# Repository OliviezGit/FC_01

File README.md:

# FC_01

Projet KiCad H743_Ardupilot.

Le [dossier composants](composants/README.md) contient les fiches techniques PDF, bibliothèques locales, STEP, vues de contrôle et la nomenclature France du 27/09/2026.

- [Contrôle PDF complet](composants/controle/CONTROLE_COMPLET.pdf)
- [BOM France et références à commander](composants/BOM_FR.csv)
- [Rapport de vérification et réserves](verification/REPORT.md)

La présence des fichiers est vérifiée. La fabrication reste non libérée et quatre références fabricant restent sans offre France confirmée.

## État PCB

- PCB : **6 couches cuivre** configurées.
- Huaqiu 90 Ω : **0,2037 mm / 0,2451 mm** enregistré dans le projet.
- Routage : **0 piste, 0 via, 0 zone**.
- Revue CEM/implantation : voir [verification/REPORT.md](verification/REPORT.md).

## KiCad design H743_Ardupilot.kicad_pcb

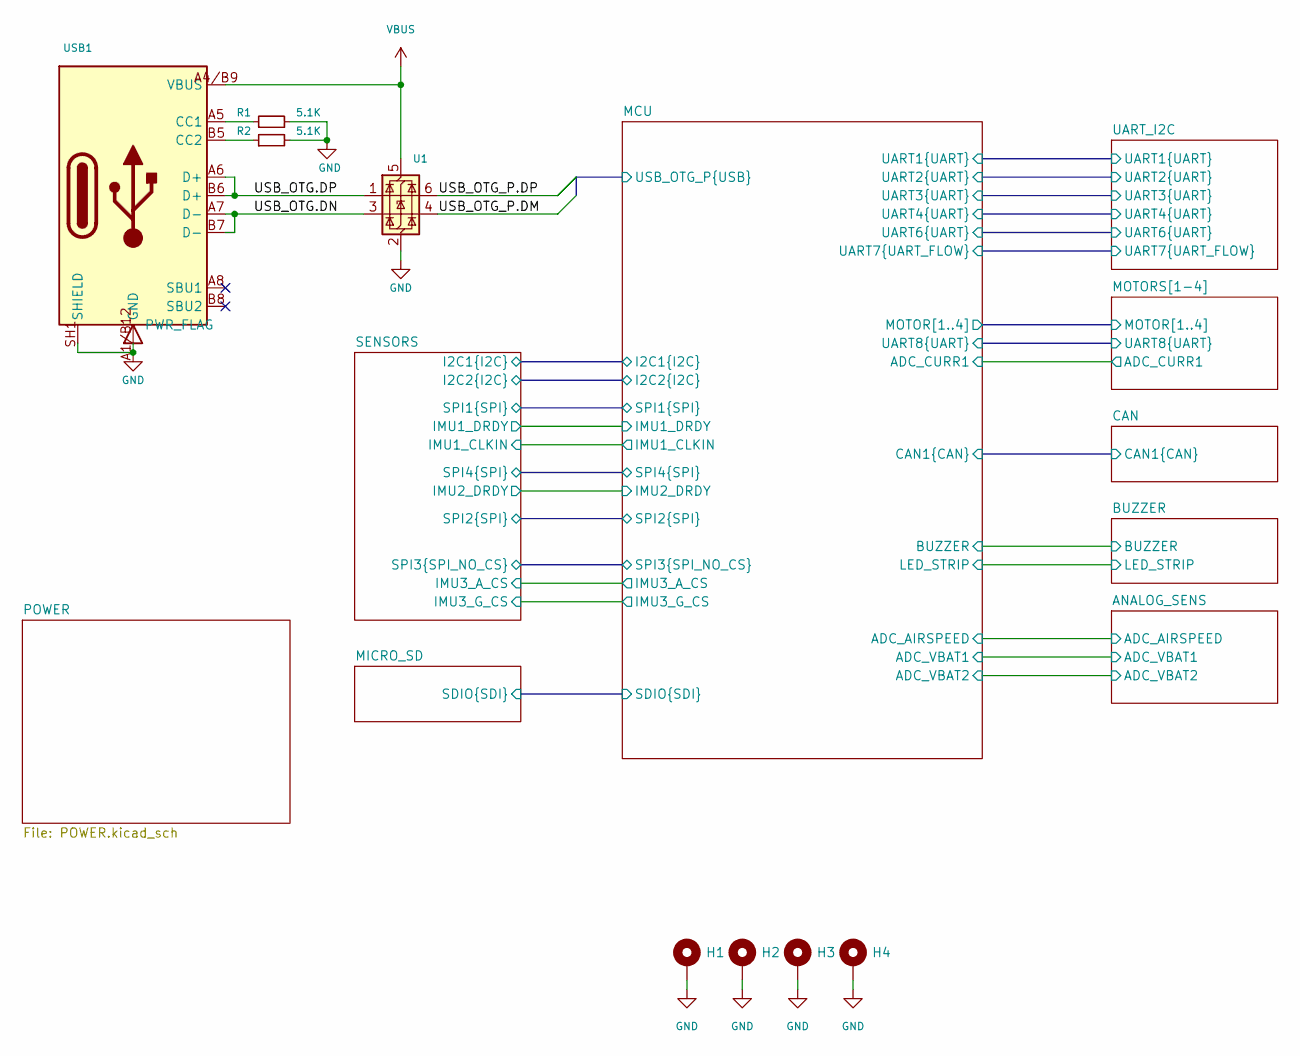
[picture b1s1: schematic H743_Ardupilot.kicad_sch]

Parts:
H1, H2, H3, H4: MountingHole_Pad; MountingHole_3.2mm_M3_ISO7380_Pad; DigiKey Status Element PCB; aucun composant achete
R1, R2: 5.1K; R_0402_1005Metric; MPN 0402WGF5101TCE; LCSC Part C25905
U1: USBLC6-2P6; SOT50P160X60-6N; MPN USBLC6-2P6; mouser 511-USBLC6-2P6
USB1: DX07S016JA1R1500; JAE_DX07S016JA1R1500_16P; MPN DX07S016JA1R1500; DigiKey Part Number 670-DX07S016JA1R1500CT-ND

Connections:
/MCU/USB_OTG_P.DM: U1.4 (I/O2); also elsewhere on the board
/MCU/USB_OTG_P.DP: U1.6 (I/O1); also elsewhere on the board
/USB_OTG.DN: U1.3 (I/O2), USB1.A7 (D-), USB1.B7 (D-)
/USB_OTG.DP: U1.1 (I/O1), USB1.A6 (D+), USB1.B6 (D+)
GND: H1.1 (1_1), H2.1 (1_1), H3.1 (1_1), H4.1 (1_1), R1.2, R2.2, U1.2 (GND), USB1.A1/B12 (GND), USB1.A12/B1 (GND), USB1.SH1 (SHIELD), USB1.SH2 (SHIELD), USB1.SH3 (SHIELD), USB1.SH4 (SHIELD), USB1.SH5 (SHIELD), USB1.SH6 (SHIELD); also elsewhere on the board
unnamed: R1.1, USB1.A5 (CC1)
unnamed: R2.1, USB1.B5 (CC2)
VBUS: U1.5 (VBUS), USB1.A4/B9 (VBUS), USB1.B4/A9 (VBUS); also elsewhere on the board

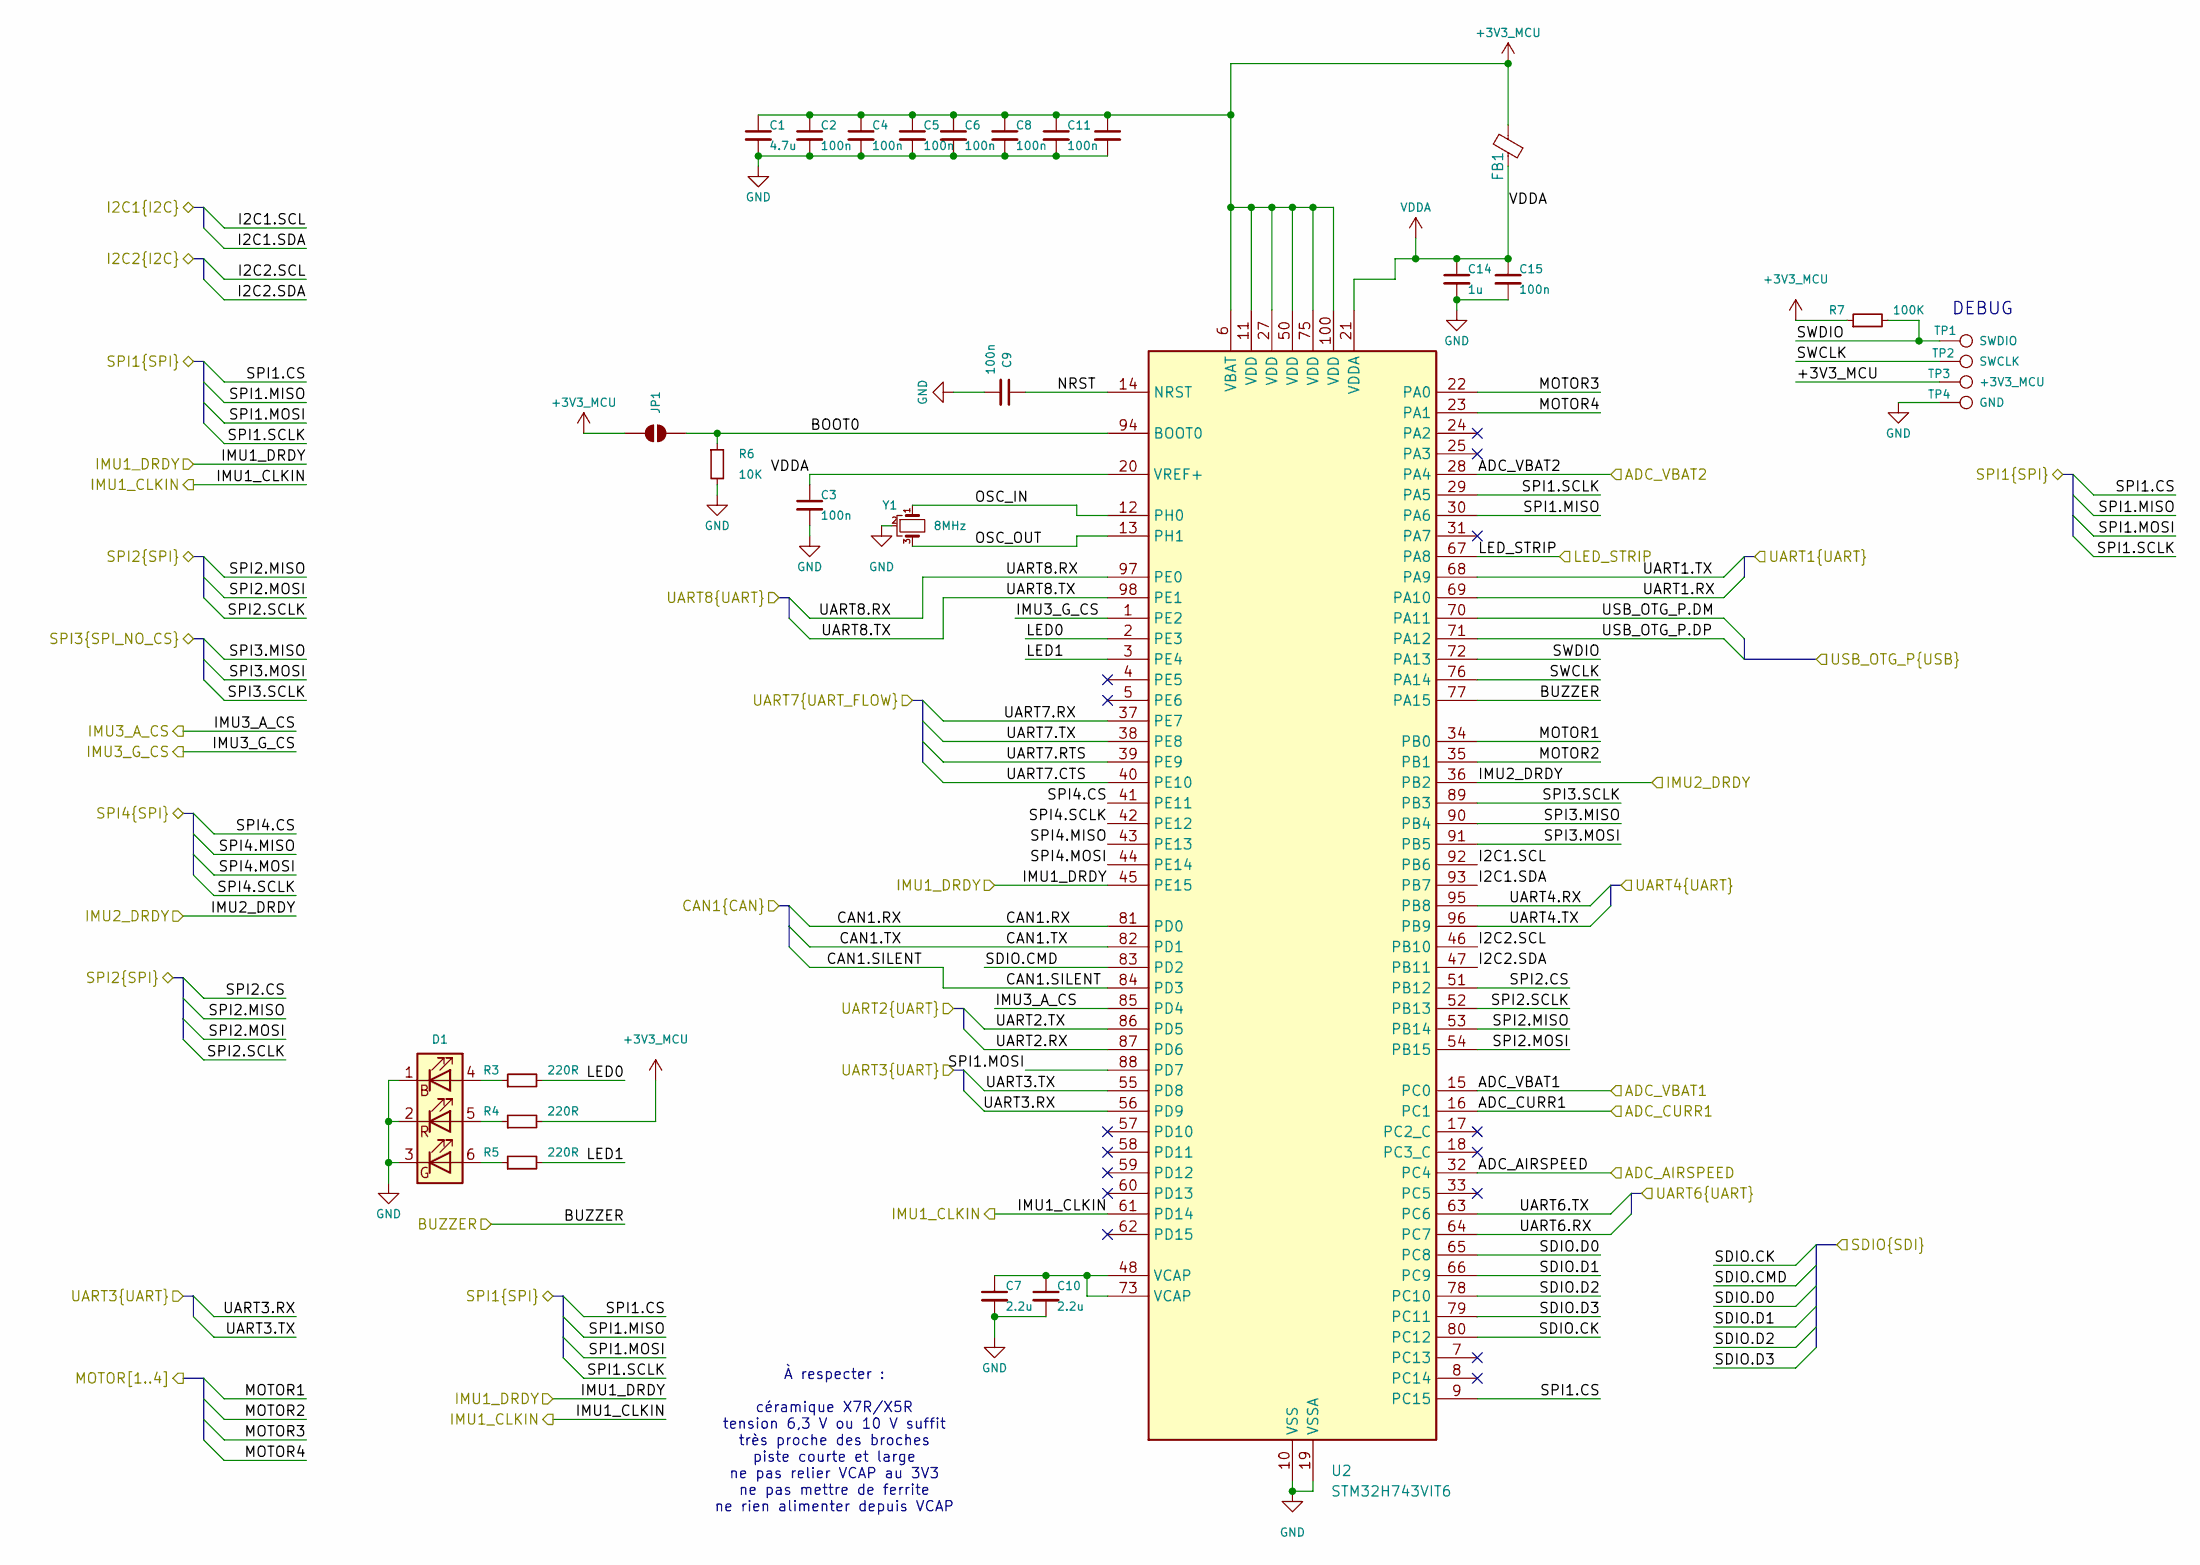
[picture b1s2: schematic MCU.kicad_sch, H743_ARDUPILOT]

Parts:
C1: 4.7u; C_0402_1005Metric; MPN CL05A475MP5NRNC; DigiKey Part Number 1276-1482-1-ND
C2, C3, C4, C5, C6, C8, C9, C11, C12, C15: 100n; C_0402_1005Metric; MPN CL05B104KO5NNNC; DigiKey Part Number 1276-1001-1-ND
C7, C10: 2.2u; C_0402_1005Metric; MPN C1005X5R1C225M050BC; DigiKey Specs 2.2 µF ±20%, 16 V, X5R, 0402
C14: 1u; C_0402_1005Metric; MPN CL05A105KA5NQNC; DigiKey Part Number 1276-1445-1-ND
D1: 19-337/R6GHBHC-M01/2T; Everlight_19-337_1.6x1.6mm; MPN 19-337/R6GHBHC-M01/2T; LCSC Part C131204
FB1: 600Ω@100MHz; L_0402_1005Metric; MPN BLM15AG601SN1D; DigiKey Part Number 490-1006-1-ND
JP1: SolderJumper_2_Open; SolderJumper-2_P1.3mm_Open_RoundedPad1.0x1.5mm; DigiKey Status Element PCB; aucun composant achete
R3, R4, R5: 220R; R_0402_1005Metric; MPN RC0402FR-07220RL; DigiKey Specs 220 Ω ±1%, 0402
R6: 10K; R_0402_1005Metric; MPN RC0402FR-0710KL; DigiKey Specs 10 kΩ ±1%, 0402
R7: 100K; R_0402_1005Metric; MPN RC0402FR-07100KL; DigiKey Specs 100 kΩ ±1%, 0402
TP1: SWDIO; TestPoint_Pad_1.0x1.0mm; DigiKey Status Element PCB; aucun composant achete
TP2: SWCLK; TestPoint_Pad_1.0x1.0mm; DigiKey Status Element PCB; aucun composant achete
TP3: +3V3_MCU; TestPoint_Pad_1.0x1.0mm; DigiKey Status Element PCB; aucun composant achete
TP4: GND; TestPoint_Pad_1.0x1.0mm; DigiKey Status Element PCB; aucun composant achete
U2: STM32H743VIT6; LQFP-100_14x14mm_P0.5mm; MPN STM32H743VIT6; DigiKey Part Number 497-17720-ND
Y1: 8MHz; Murata_CSTNE_3.2x1.3_P1.2mm; MPN CSTNE8M00GH5C000R0; LCSC Part C341525

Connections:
+3V3_MCU: C1.1, C2.1, C4.1, C5.1, C6.1, C8.1, C11.1, C12.1, FB1.2, JP1.2 (B), R4.2, R7.1, TP3.1 (1_1), U2.6 (VBAT), U2.11 (VDD), U2.27 (VDD), U2.50 (VDD), U2.75 (VDD), U2.100 (VDD); also elsewhere on the board
/ANALOG_SENS/ADC_AIRSPEED: U2.32 (PC4); also elsewhere on the board
/ANALOG_SENS/ADC_VBAT1: U2.15 (PC0); also elsewhere on the board
/ANALOG_SENS/ADC_VBAT2: U2.28 (PA4); also elsewhere on the board
/BUZZER/BUZZER: U2.77 (PA15); also elsewhere on the board
/BUZZER/LED_STRIP: U2.67 (PA8); also elsewhere on the board
/CAN/CAN1.RX: U2.81 (PD0); also elsewhere on the board
/CAN/CAN1.SILENT: U2.84 (PD3); also elsewhere on the board
/CAN/CAN1.TX: U2.82 (PD1); also elsewhere on the board
/MCU/ADC_CURR1: U2.16 (PC1); also elsewhere on the board
/MCU/BOOT0: JP1.1 (A), R6.1, U2.94 (BOOT0)
/MCU/I2C1.SCL: U2.92 (PB6); also elsewhere on the board
/MCU/I2C1.SDA: U2.93 (PB7); also elsewhere on the board
/MCU/I2C2.SCL: U2.46 (PB10); also elsewhere on the board
/MCU/I2C2.SDA: U2.47 (PB11); also elsewhere on the board
/MCU/IMU1_CLKIN: U2.61 (PD14); also elsewhere on the board
/MCU/IMU1_DRDY: U2.45 (PE15); also elsewhere on the board
/MCU/IMU2_DRDY: U2.36 (PB2); also elsewhere on the board
/MCU/IMU3_A_CS: U2.85 (PD4); also elsewhere on the board
/MCU/IMU3_G_CS: U2.1 (PE2); also elsewhere on the board
/MCU/LED0: R3.2, U2.2 (PE3)
/MCU/LED1: R5.2, U2.3 (PE4)
/MCU/MOTOR1: U2.34 (PB0); also elsewhere on the board
/MCU/MOTOR2: U2.35 (PB1); also elsewhere on the board
/MCU/MOTOR3: U2.22 (PA0); also elsewhere on the board
/MCU/MOTOR4: U2.23 (PA1); also elsewhere on the board
/MCU/NRST: C9.1, U2.14 (NRST)
/MCU/OSC_IN: U2.12 (PH0), Y1.1
/MCU/OSC_OUT: U2.13 (PH1), Y1.3
/MCU/SDIO.CK: U2.80 (PC12); also elsewhere on the board
/MCU/SDIO.CMD: U2.83 (PD2); also elsewhere on the board
/MCU/SDIO.D0: U2.65 (PC8); also elsewhere on the board
/MCU/SDIO.D1: U2.66 (PC9); also elsewhere on the board
/MCU/SDIO.D2: U2.78 (PC10); also elsewhere on the board
/MCU/SDIO.D3: U2.79 (PC11); also elsewhere on the board
/MCU/SPI1.CS: U2.9 (PC15); also elsewhere on the board
/MCU/SPI1.MISO: U2.30 (PA6); also elsewhere on the board
/MCU/SPI1.MOSI: U2.88 (PD7); also elsewhere on the board
/MCU/SPI1.SCLK: U2.29 (PA5); also elsewhere on the board
/MCU/SPI2.CS: U2.51 (PB12); also elsewhere on the board
/MCU/SPI2.MISO: U2.53 (PB14); also elsewhere on the board
/MCU/SPI2.MOSI: U2.54 (PB15); also elsewhere on the board
/MCU/SPI2.SCLK: U2.52 (PB13); also elsewhere on the board
/MCU/SPI3.MISO: U2.90 (PB4); also elsewhere on the board
/MCU/SPI3.MOSI: U2.91 (PB5); also elsewhere on the board
/MCU/SPI3.SCLK: U2.89 (PB3); also elsewhere on the board
/MCU/SPI4.CS: U2.41 (PE11); also elsewhere on the board
/MCU/SPI4.MISO: U2.43 (PE13); also elsewhere on the board
/MCU/SPI4.MOSI: U2.44 (PE14); also elsewhere on the board
/MCU/SPI4.SCLK: U2.42 (PE12); also elsewhere on the board
/MCU/SWCLK: TP2.1 (1_1), U2.76 (PA14)
/MCU/SWDIO: R7.2, TP1.1 (1_1), U2.72 (PA13)
/MCU/UART1.RX: U2.69 (PA10); also elsewhere on the board
/MCU/UART1.TX: U2.68 (PA9); also elsewhere on the board
/MCU/UART2.RX: U2.87 (PD6); also elsewhere on the board
/MCU/UART2.TX: U2.86 (PD5); also elsewhere on the board
/MCU/UART3.RX: U2.56 (PD9); also elsewhere on the board
/MCU/UART3.TX: U2.55 (PD8); also elsewhere on the board
/MCU/UART4.RX: U2.95 (PB8); also elsewhere on the board
/MCU/UART4.TX: U2.96 (PB9); also elsewhere on the board
/MCU/UART6.RX: U2.64 (PC7); also elsewhere on the board
/MCU/UART6.TX: U2.63 (PC6); also elsewhere on the board
/MCU/UART7.CTS: U2.40 (PE10); also elsewhere on the board
/MCU/UART7.RTS: U2.39 (PE9); also elsewhere on the board
/MCU/UART7.RX: U2.37 (PE7); also elsewhere on the board
/MCU/UART7.TX: U2.38 (PE8); also elsewhere on the board
/MCU/UART8.RX: U2.97 (PE0); also elsewhere on the board
/MCU/UART8.TX: U2.98 (PE1)
/MCU/USB_OTG_P.DM: U2.70 (PA11); also elsewhere on the board
/MCU/USB_OTG_P.DP: U2.71 (PA12); also elsewhere on the board
GND: C1.2, C2.2, C3.2, C4.2, C5.2, C6.2, C7.2, C8.2, C9.2, C10.2, C11.2, C12.2, C14.2, C15.2, D1.1 (BK), D1.2 (RK), D1.3 (GK), R6.2, TP4.1 (1_1), U2.10 (VSS), U2.19 (VSSA), U2.26 (VSS), U2.49 (VSS), U2.74 (VSS), U2.99 (VSS), Y1.2; also elsewhere on the board
unnamed: C7.1, C10.1, U2.48 (VCAP), U2.73 (VCAP)
unnamed: D1.4 (BA), R3.1
unnamed: D1.6 (GA), R5.1
unnamed: D1.5 (RA), R4.1
VDDA: C3.1, C14.1, C15.1, FB1.1, U2.20 (VREF+), U2.21 (VDDA)

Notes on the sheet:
DEBUG
À respecter : céramique X7R/X5R tension 6,3 V ou 10 V suffit très proche des broches piste courte et large ne pas relier VCAP au 3V3 ne pas mettre de ferrite ne rien alimenter depuis VCAP

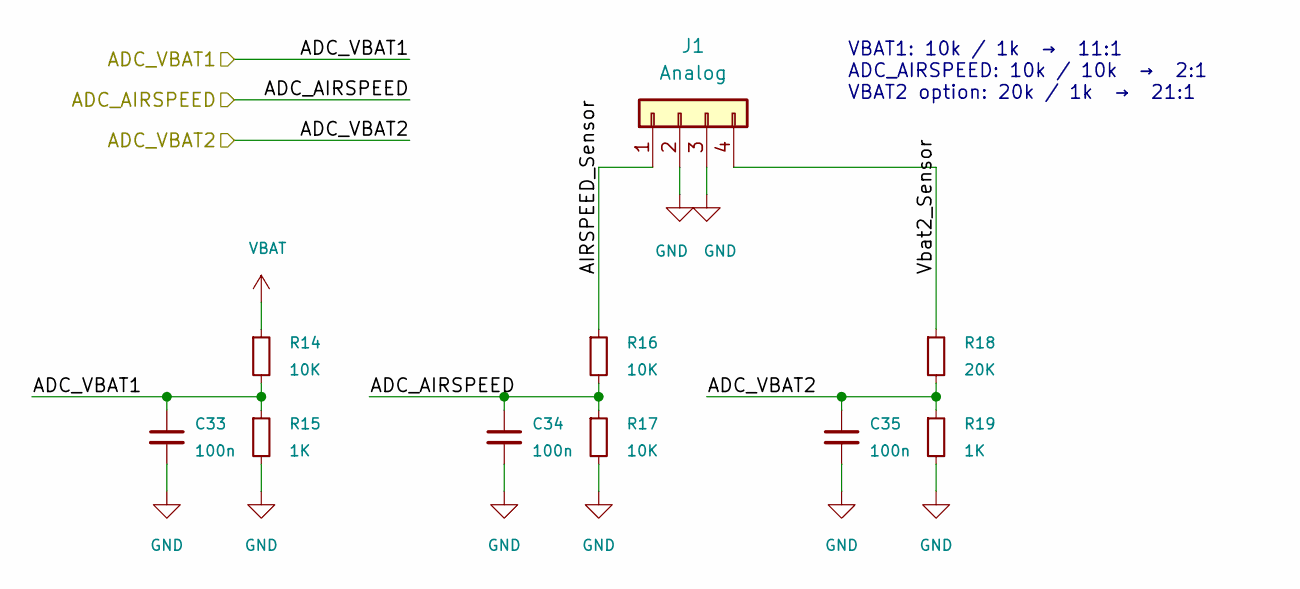
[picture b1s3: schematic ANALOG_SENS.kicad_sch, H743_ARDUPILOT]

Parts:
C33, C34, C35: 100n; C_0402_1005Metric; MPN CL05B104KO5NNNC; DigiKey Part Number 1276-1001-1-ND
J1: Analog; SolderPadArray_1x04_P2.54mm_1x1mm; DigiKey Status Element PCB; aucun composant achete
R14, R16, R17: 10K; R_0402_1005Metric; MPN RC0402FR-0710KL; DigiKey Specs 10 kΩ ±1%, 0402
R15, R19: 1K; R_0402_1005Metric; MPN RC0402FR-071KL; DigiKey Specs 1 kΩ ±1%, 0402
R18: 20K; R_0402_1005Metric; MPN RC0402FR-0720KL; DigiKey Specs 20 kΩ ±1%, 0402

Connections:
/ANALOG_SENS/ADC_AIRSPEED: C34.1, R16.2, R17.1; also elsewhere on the board
/ANALOG_SENS/ADC_VBAT1: C33.1, R14.2, R15.1; also elsewhere on the board
/ANALOG_SENS/ADC_VBAT2: C35.1, R18.2, R19.1; also elsewhere on the board
/ANALOG_SENS/AIRSPEED_Sensor: J1.1, R16.1
/ANALOG_SENS/Vbat2_Sensor: J1.4, R18.1
GND: C33.2, C34.2, C35.2, J1.2, J1.3, R15.2, R17.2, R19.2; also elsewhere on the board
VBAT: R14.1; also elsewhere on the board

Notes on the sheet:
VBAT1: 10k / 1k → 11:1 ADC_AIRSPEED: 10k / 10k → 2:1 VBAT2 option: 20k / 1k → 21:1

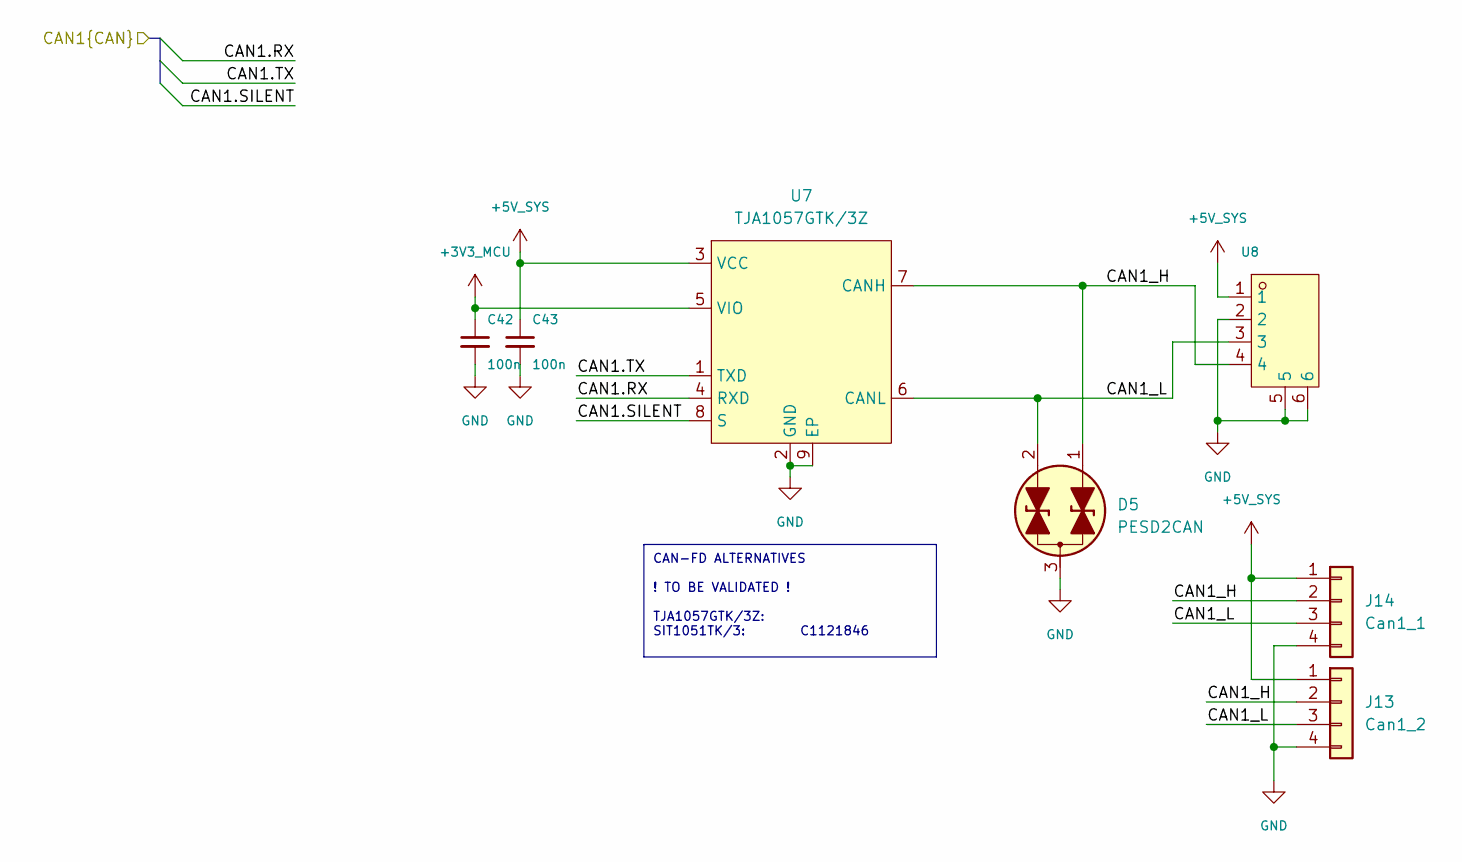
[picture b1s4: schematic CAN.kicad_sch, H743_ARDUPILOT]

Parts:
C42, C43: 100n; C_0402_1005Metric; MPN CL05B104KO5NNNC; DigiKey Part Number 1276-1001-1-ND
D5: PESD2CAN; SOT-23; MPN PESD2CANFD24V-TR; LCSC Part C552486
J13: Can1_2; SolderPadArray_1x04_P2.54mm_1x1mm; DigiKey Status Element PCB; aucun composant achete
J14: Can1_1; SolderPadArray_1x04_P2.54mm_1x1mm; DigiKey Status Element PCB; aucun composant achete
U7: TJA1057GTK/3Z; HVSON-8-1EP_3x3mm_P0.65mm_EP1.6x2.4mm; MPN TJA1057GTK/3Z; DigiKey Specs CAN 5 Mbps, 4.5–5.5 V, 8-HVSON 3x3
U8: SM04B-GHS-TB(LF)(SN); JST_GH_SM04B-GHS-TB_1x04_P1.25mm_Horizontal_GNDtabs; MPN SM04B-GHS-TB(LF)(SN); LCSC Part C7430446

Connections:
+3V3_MCU: C42.1, U7.5 (VIO); also elsewhere on the board
+5V_SYS: C43.1, J13.1, J14.1, U7.3 (VCC), U8.1; also elsewhere on the board
/CAN/CAN1.RX: U7.4 (RXD); also elsewhere on the board
/CAN/CAN1.SILENT: U7.8 (S); also elsewhere on the board
/CAN/CAN1.TX: U7.1 (TXD); also elsewhere on the board
/CAN/CAN1_H: D5.1 (K1), J13.2, J14.2, U7.7 (CANH), U8.4
/CAN/CAN1_L: D5.2 (K2), J13.3, J14.3, U7.6 (CANL), U8.3
GND: C42.2, C43.2, D5.3 (CC), J13.4, J14.4, U7.2 (GND), U7.9 (EP), U8.2, U8.5, U8.6; also elsewhere on the board

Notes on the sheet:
CAN-FD ALTERNATIVES ! TO BE VALIDATED ! TJA1057GTK/3Z: SIT1051TK/3: C1121846

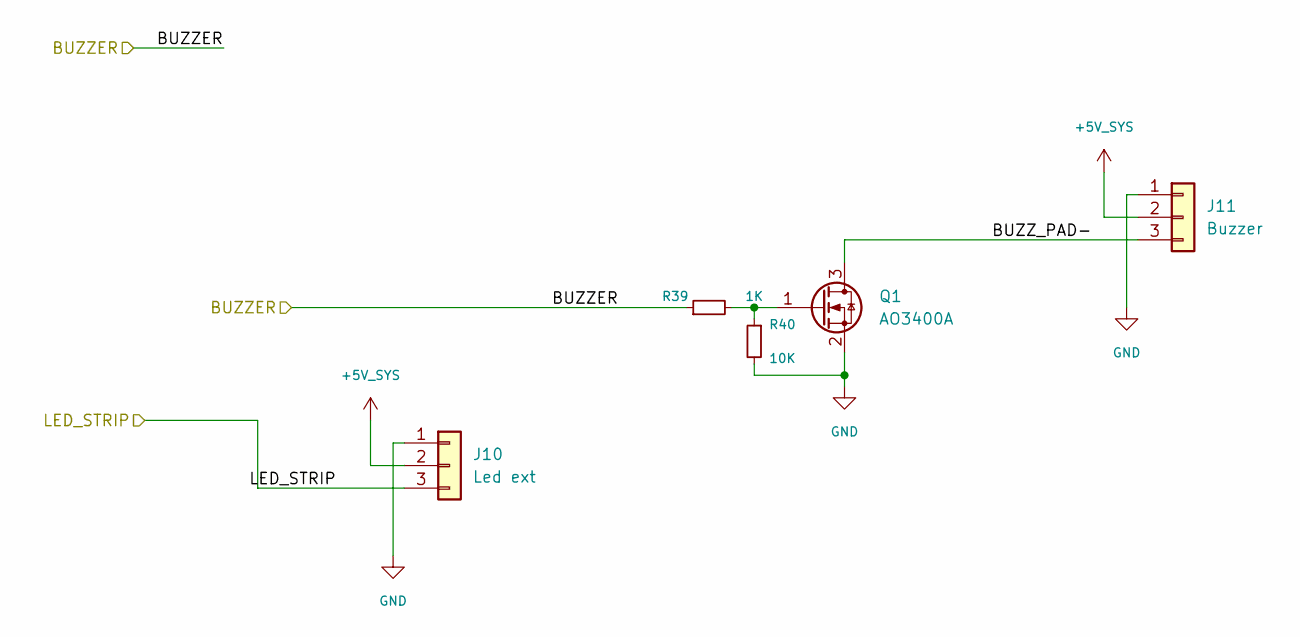
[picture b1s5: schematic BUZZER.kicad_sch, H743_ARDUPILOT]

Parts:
J10: Led ext; SolderPadArray_1x03_P2.54mm_1x1mm; DigiKey Status Element PCB; aucun composant achete
J11: Buzzer; SolderPadArray_1x03_P2.54mm_1x1mm; DigiKey Status Element PCB; aucun composant achete
Q1: AO3400A; SOT-23; MPN AO3400A; LCSC Part C20917
R39: 1K; R_0402_1005Metric; MPN RC0402FR-071KL; DigiKey Specs 1K ±1%, 0402 (1005), thick film
R40: 10K; R_0402_1005Metric; MPN RC0402FR-0710KL; DigiKey Specs 10K ±1%, 0402 (1005), thick film

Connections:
+5V_SYS: J10.2, J11.2; also elsewhere on the board
/BUZZER/BUZZER: R39.1; also elsewhere on the board
/BUZZER/BUZZ_PAD-: J11.3, Q1.3 (D)
/BUZZER/LED_STRIP: J10.3; also elsewhere on the board
GND: J10.1, J11.1, Q1.2 (S), R40.2; also elsewhere on the board
unnamed: Q1.1 (G), R39.2, R40.1

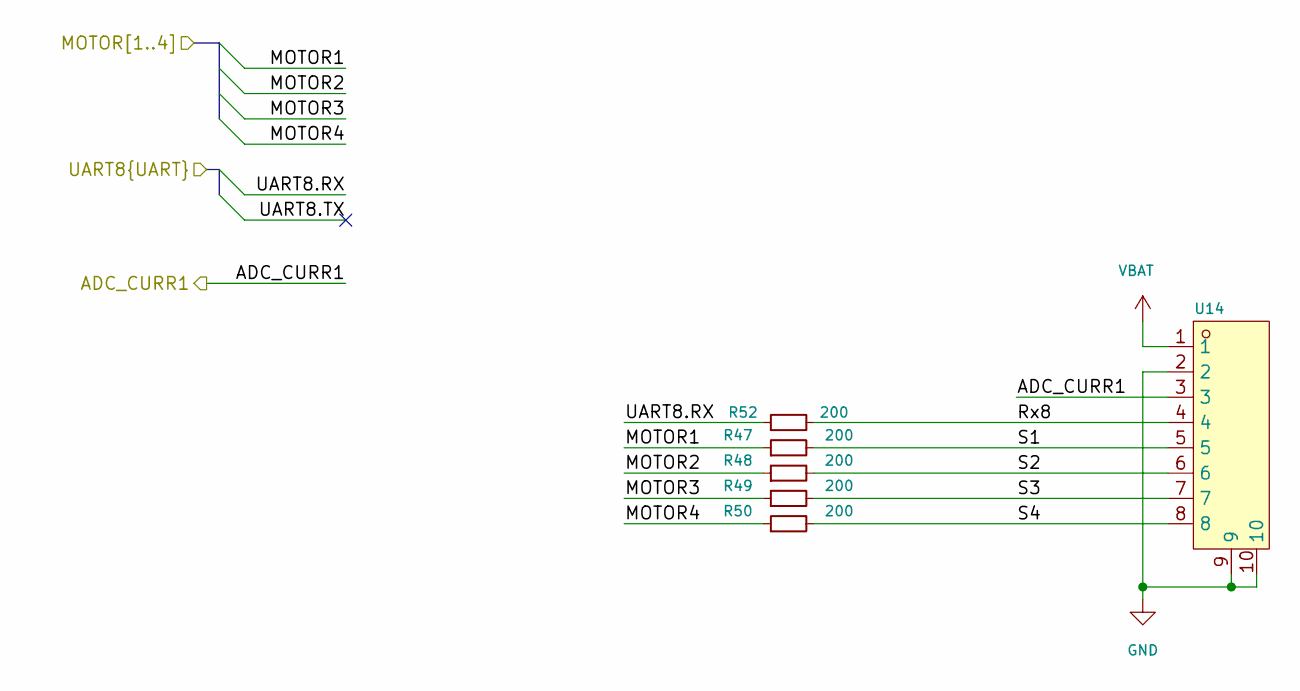
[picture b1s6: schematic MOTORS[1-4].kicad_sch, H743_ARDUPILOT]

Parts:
R47, R48, R49, R50, R52: 200; R_0402_1005Metric; MPN RC0402FR-07200RL; DigiKey Specs 200 ±1%, 0402 (1005), thick film
U14: SM08B-SRSS-TB(LF)(SN); JST_SH_SM08B-SRSS-TB_1x08_P1.00mm_Horizontal_GNDtabs; MPN SM08B-SRSS-TB(LF)(SN); LCSC Part C7430450

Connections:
/MCU/ADC_CURR1: U14.3; also elsewhere on the board
/MCU/MOTOR1: R47.1; also elsewhere on the board
/MCU/MOTOR2: R48.1; also elsewhere on the board
/MCU/MOTOR3: R49.1; also elsewhere on the board
/MCU/MOTOR4: R50.1; also elsewhere on the board
/MCU/UART8.RX: R52.1; also elsewhere on the board
/MOTORS[1-4]/Rx8: R52.2, U14.4
/MOTORS[1-4]/S1: R47.2, U14.5
/MOTORS[1-4]/S2: R48.2, U14.6
/MOTORS[1-4]/S3: R49.2, U14.7
/MOTORS[1-4]/S4: R50.2, U14.8
GND: U14.2, U14.9, U14.10; also elsewhere on the board
VBAT: U14.1; also elsewhere on the board

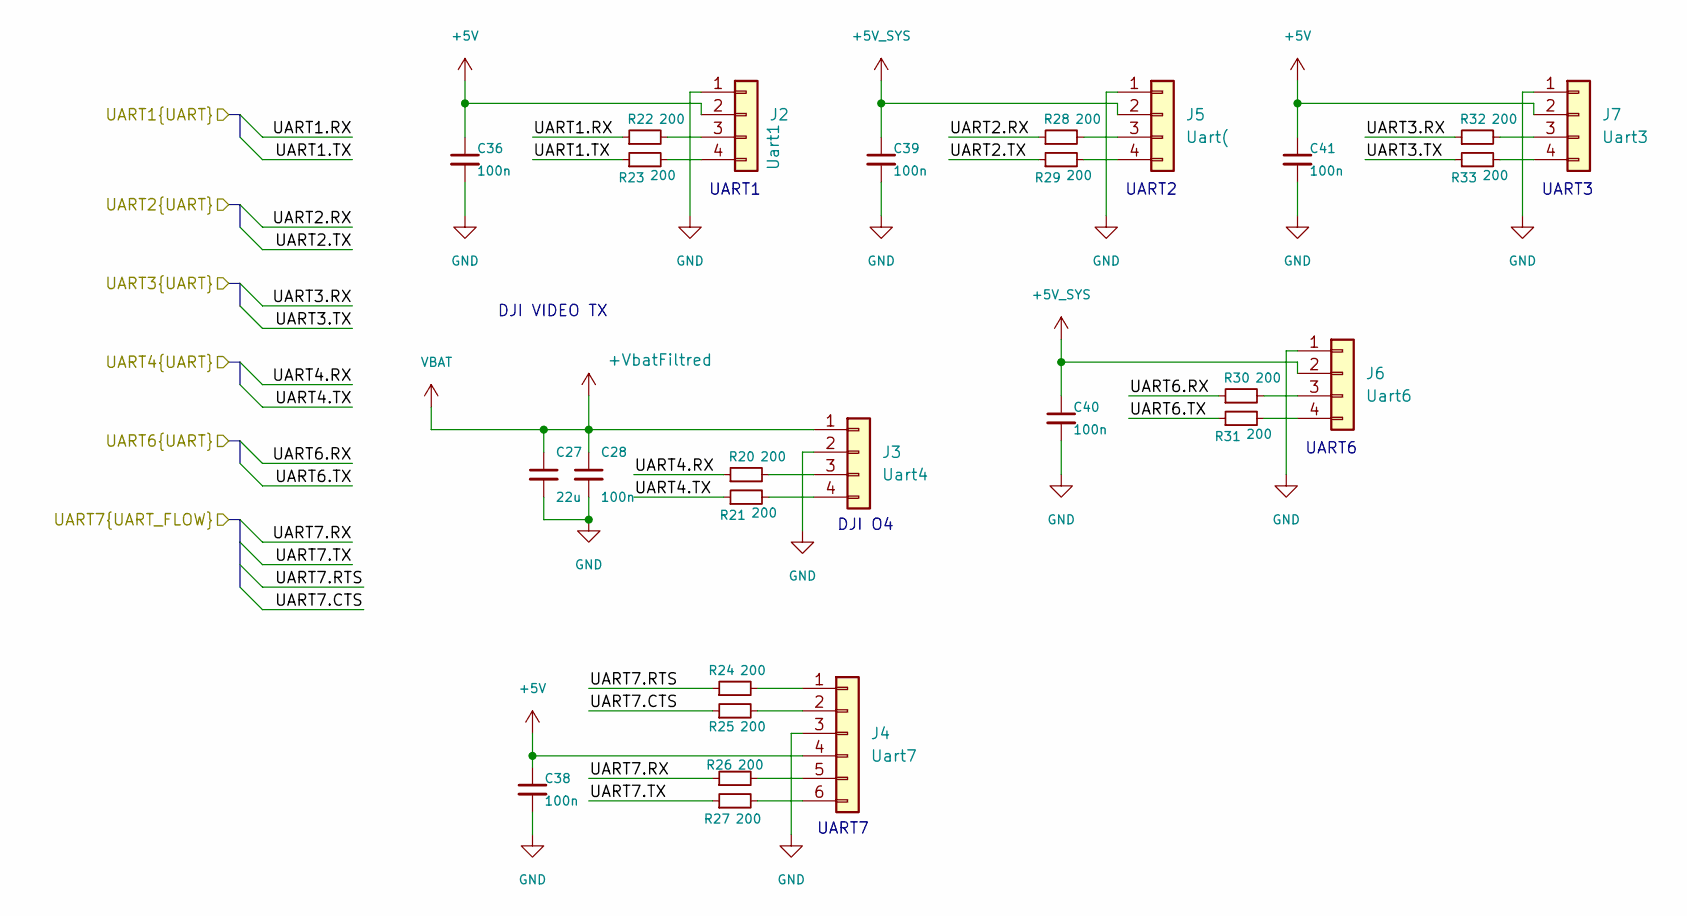
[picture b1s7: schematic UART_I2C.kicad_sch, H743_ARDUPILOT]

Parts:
C27: 22u; C_0805_2012Metric; MPN CL21A226MAYNNNE; DigiKey Part Number 1276-CL21A226MAYNNNECT-ND
C28: 100n; C_0402_1005Metric; MPN GCM155R71H104KE02D; DigiKey Part Number 490-10672-1-ND
C36, C38, C39, C40, C41: 100n; C_0402_1005Metric; MPN CL05B104KO5NNNC; DigiKey Part Number 1276-1001-1-ND
J2: Uart1; SolderPadArray_1x04_P2.54mm_1x1mm; DigiKey Status Element PCB; aucun composant achete
J3: Uart4; SolderPadArray_1x04_P2.54mm_1x1mm; DigiKey Status Element PCB; aucun composant achete
J4: Uart7; SolderPadArray_1x06_P2.54mm_1x1mm; DigiKey Status Element PCB; aucun composant achete
J5: Uart(; SolderPadArray_1x04_P2.54mm_1x1mm; DigiKey Status Element PCB; aucun composant achete
J6: Uart6; SolderPadArray_1x04_P2.54mm_1x1mm; DigiKey Status Element PCB; aucun composant achete
J7: Uart3; SolderPadArray_1x04_P2.54mm_1x1mm; DigiKey Status Element PCB; aucun composant achete
R20, R21, R22, R23, R24, R25, R26, R27, R28, R29, R30, R31, R32, R33: 200; R_0402_1005Metric; MPN RC0402FR-07200RL; DigiKey Specs 200 ±1%, 0402 (1005), thick film

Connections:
+5V: C36.1, C38.1, C41.1, J2.2, J4.4, J7.2; also elsewhere on the board
+5V_SYS: C39.1, C40.1, J5.2, J6.2; also elsewhere on the board
+9V: C27.1, C28.1, J3.1; also elsewhere on the board
/MCU/UART1.RX: R22.1; also elsewhere on the board
/MCU/UART1.TX: R23.1; also elsewhere on the board
/MCU/UART2.RX: R28.1; also elsewhere on the board
/MCU/UART2.TX: R29.1; also elsewhere on the board
/MCU/UART3.RX: R32.1; also elsewhere on the board
/MCU/UART3.TX: R33.1; also elsewhere on the board
/MCU/UART4.RX: R20.1; also elsewhere on the board
/MCU/UART4.TX: R21.1; also elsewhere on the board
/MCU/UART6.RX: R30.1; also elsewhere on the board
/MCU/UART6.TX: R31.1; also elsewhere on the board
/MCU/UART7.CTS: R25.1; also elsewhere on the board
/MCU/UART7.RTS: R24.1; also elsewhere on the board
/MCU/UART7.RX: R26.1; also elsewhere on the board
/MCU/UART7.TX: R27.1; also elsewhere on the board
GND: C27.2, C28.2, C36.2, C38.2, C39.2, C40.2, C41.2, J2.1, J3.2, J4.3, J5.1, J6.1, J7.1; also elsewhere on the board
unnamed: J2.3, R22.2
unnamed: J2.4, R23.2
unnamed: J3.3, R20.2
unnamed: J3.4, R21.2
unnamed: J4.1, R24.2
unnamed: J4.2, R25.2
unnamed: J4.5, R26.2
unnamed: J4.6, R27.2
unnamed: J5.3, R28.2
unnamed: J5.4, R29.2
unnamed: J6.3, R30.2
unnamed: J6.4, R31.2
unnamed: J7.3, R32.2
unnamed: J7.4, R33.2

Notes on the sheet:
DJI O4
UART3
UART1
UART6
UART2
UART7
DJI VIDEO TX

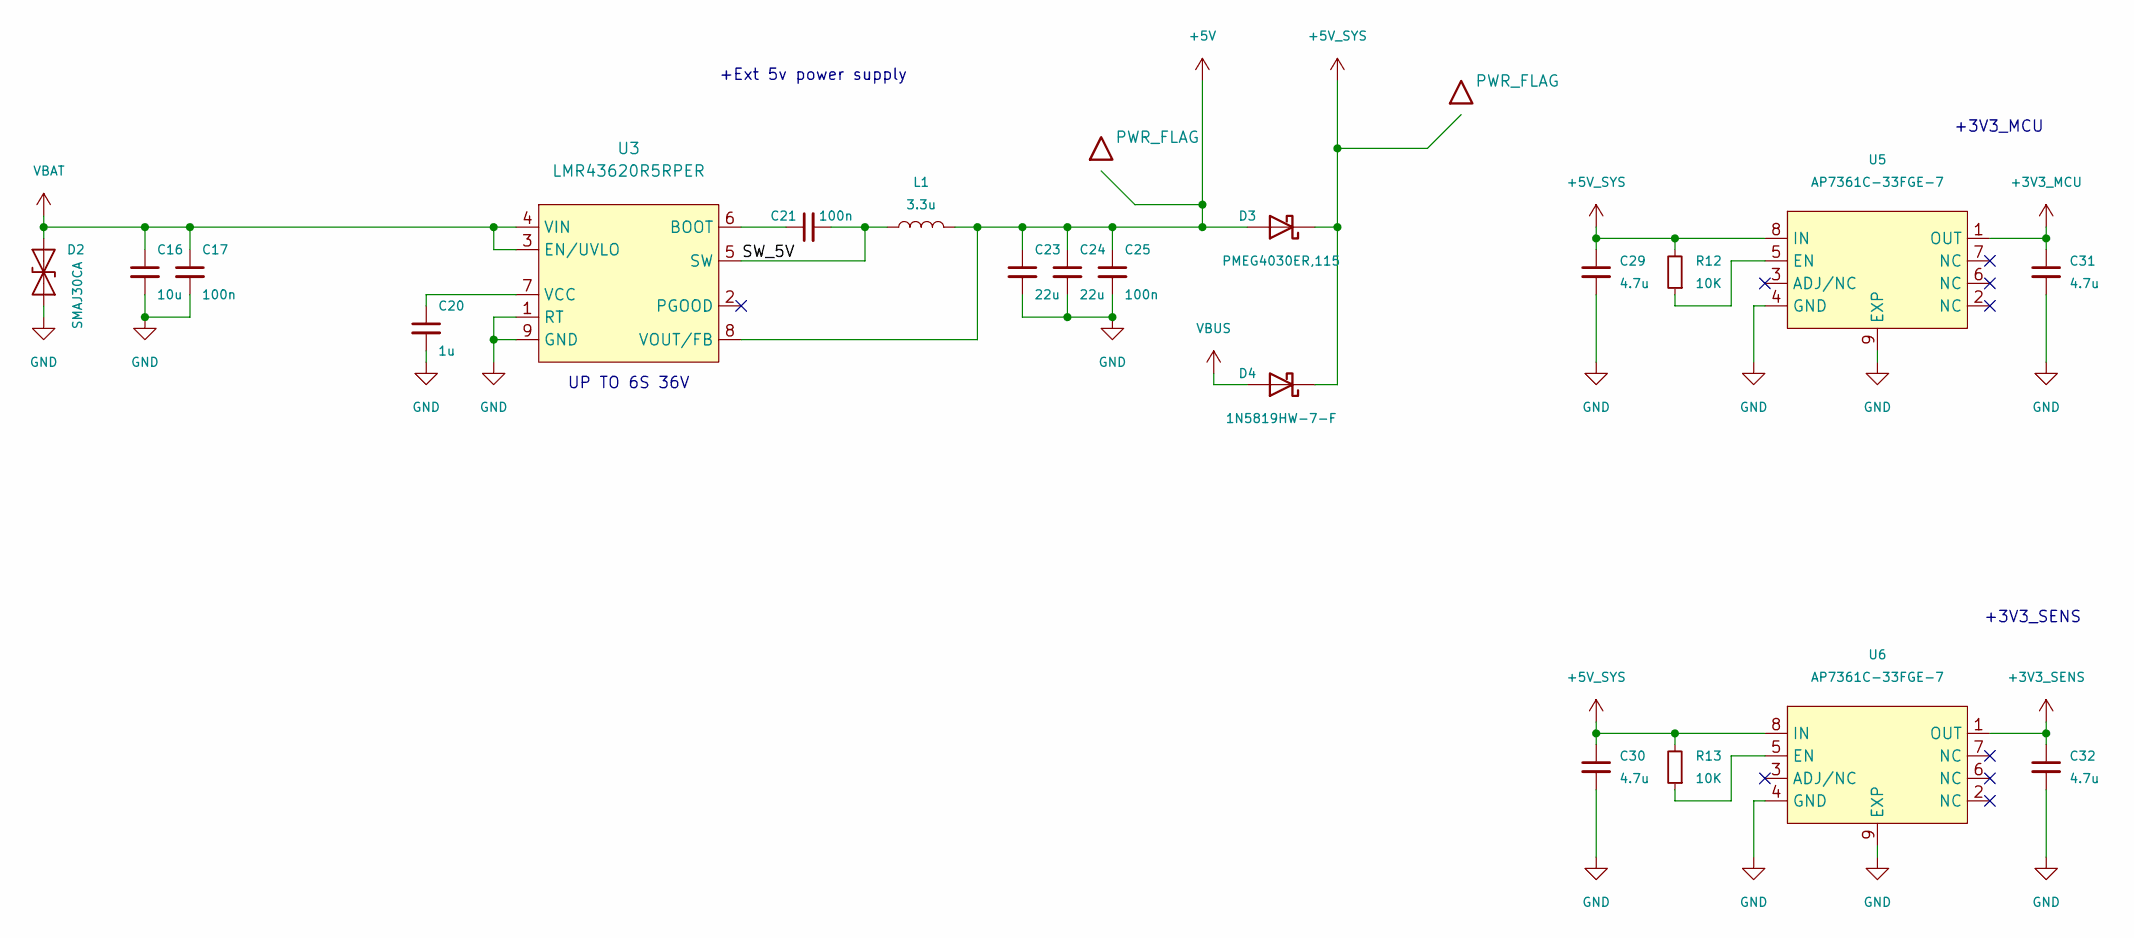
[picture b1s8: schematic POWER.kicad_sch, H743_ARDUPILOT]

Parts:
C16: 10u; C_0805_2012Metric; MPN GRM21BR61H106KE43L; DigiKey Part Number 490-18663-1-ND
C17, C21, C25: 100n; C_0402_1005Metric; MPN GCM155R71H104KE02D; DigiKey Part Number 490-10672-1-ND
C20: 1u; C_0603_1608Metric; MPN CL10A105KB8NNNC; DigiKey Part Number 1276-1860-1-ND
C23, C24: 22u; C_0805_2012Metric; MPN CL21A226MAYNNNE; DigiKey Part Number 1276-CL21A226MAYNNNECT-ND
C29, C30, C31, C32: 4.7u; C_0603_1608Metric; MPN CL10A475KO8NNNC; DigiKey Part Number 1276-1784-1-ND
D2: SMAJ30CA; Diodes_SMA_SMAJ30CA; MPN SMAJ30CA-13-F; LCSC Part C134980
D3: PMEG4030ER,115; Nexperia_CFP3_SOD-123W; MPN PMEG4030ER,115; DigiKey Part Number 1727-5313-1-ND
D4: 1N5819HW-7-F; D_SOD-123; MPN 1N5819HW-7-F; DigiKey Part Number 1N5819HW-FDICT-ND
L1: 3.3u; L_Coilcraft_XGL4030; MPN XGL4030-332MEC; LCSC C6012410
R12, R13: 10K; R_0402_1005Metric; MPN RC0402FR-0710KL; DigiKey Specs 10K ±1%, 0402 (1005), thick film
U3: LMR43620R5RPER; TI_RPE0009B_VQFN-HR-9_2x2mm; MPN LMR43620R5RPER; LCSC Part C32712896
U5, U6: AP7361C-33FGE-7; Diodes_U-DFN3030-8_TypeE; MPN AP7361C-33FGE-7; LCSC Part C151007

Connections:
+3V3_MCU: C31.1, U5.1 (OUT); also elsewhere on the board
+3V3_SENS: C32.1, U6.1 (OUT); also elsewhere on the board
+5V: C23.1, C24.1, C25.1, D3.2 (A), L1.2, U3.8 (VOUT/FB); also elsewhere on the board
+5V_SYS: C29.1, C30.1, D3.1 (K), D4.1 (K), R12.2, R13.2, U5.8 (IN), U6.8 (IN); also elsewhere on the board
/POWER/SW_5V: C21.2, L1.1, U3.5 (SW)
GND: C16.2, C17.2, C20.2, C23.2, C24.2, C25.2, C29.2, C30.2, C31.2, C32.2, D2.1 (A1), U3.1 (RT), U3.9 (GND), U5.4 (GND), U5.9 (EXP), U6.4 (GND), U6.9 (EXP); also elsewhere on the board
unnamed: C21.1, U3.6 (BOOT)
unnamed: C20.1, U3.7 (VCC)
unnamed: R12.1, U5.5 (EN)
unnamed: R13.1, U6.5 (EN)
VBAT: C16.1, C17.1, D2.2 (A2), U3.3 (EN/UVLO), U3.4 (VIN); also elsewhere on the board
VBUS: D4.2 (A); also elsewhere on the board

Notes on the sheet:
+3V3_SENS
+Ext 5v power supply
+3V3_MCU
UP TO 6S 36V

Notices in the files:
LEVIA_H7.kicad_pcb:
License: CERN-OHL-S-2.0
